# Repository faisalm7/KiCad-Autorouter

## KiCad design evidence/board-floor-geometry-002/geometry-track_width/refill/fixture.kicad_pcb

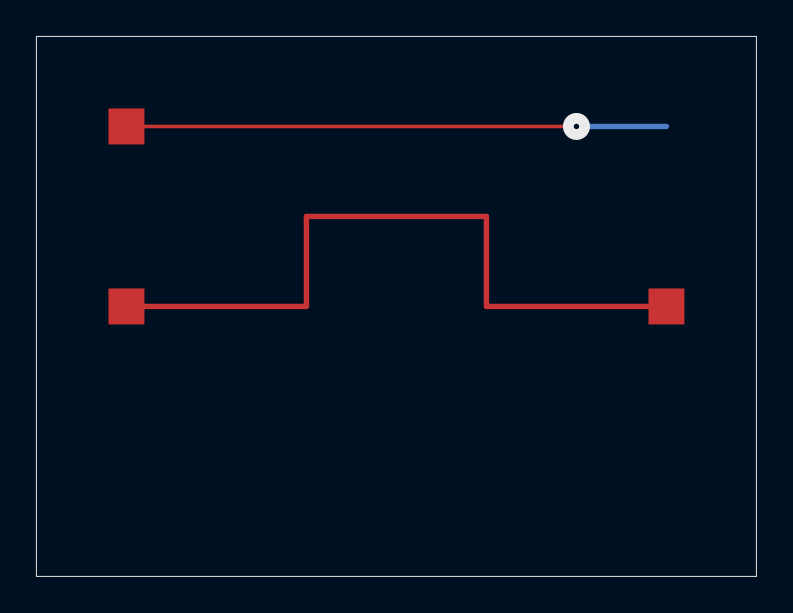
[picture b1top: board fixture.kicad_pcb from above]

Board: 2 copper layers, 40.0 x 30.0 mm, 4 parts (1 on the bottom side), 2 nets.

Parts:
J1, J2, J3, J4: floor_control_terminal

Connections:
SIGNAL_A: J1.1, J2.1
SIGNAL_B: J3.1, J4.1
